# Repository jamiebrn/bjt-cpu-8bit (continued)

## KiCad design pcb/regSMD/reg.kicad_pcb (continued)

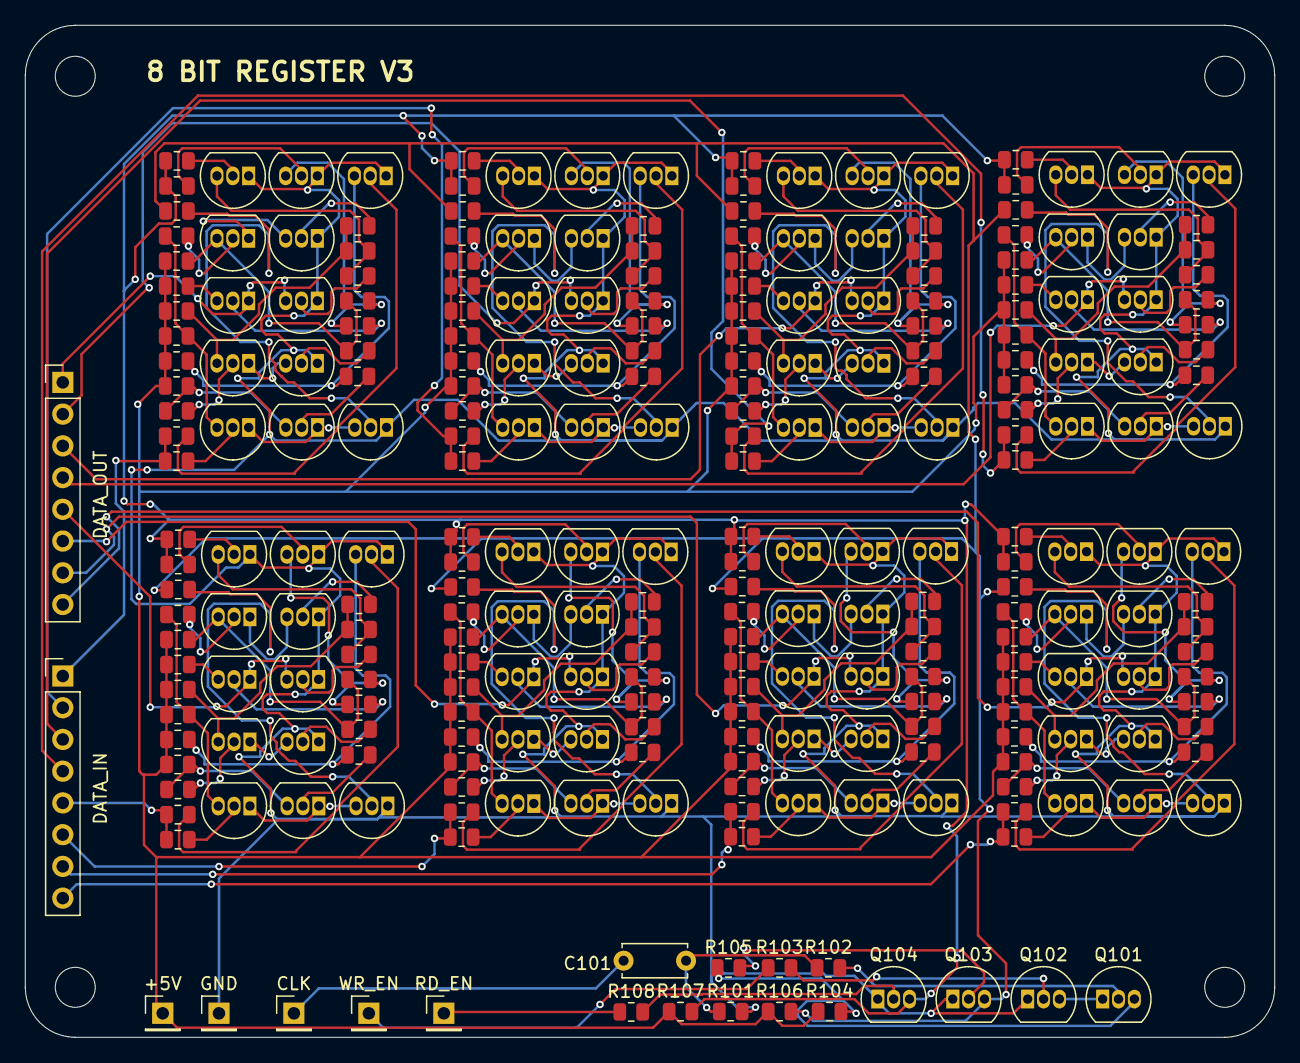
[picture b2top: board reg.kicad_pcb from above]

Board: 2 copper layers, 100.0 x 81.0 mm, 276 parts (0 on the bottom side), 214 nets.

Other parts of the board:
+5V: CLK; PinHeader_1x01_P2.54mm_Vertical
CLK: CLK; PinHeader_1x01_P2.54mm_Vertical
DATA_IN: Conn_01x08_Pin; PinHeader_1x08_P2.54mm_Vertical
DATA_OUT: Conn_01x08_Pin; PinHeader_1x08_P2.54mm_Vertical
GND: WRITE_EN; PinHeader_1x01_P2.54mm_Vertical
RD_EN: READ_EN; PinHeader_1x01_P2.54mm_Vertical
WR_EN: WRITE_EN; PinHeader_1x01_P2.54mm_Vertical

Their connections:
+5V: +5V.1; also elsewhere on the board
/DFlipFlop1/D: DATA_IN.2; also elsewhere on the board
/DFlipFlop1/Q: DATA_OUT.2; also elsewhere on the board
/DFlipFlop2/D: DATA_IN.3; also elsewhere on the board
/DFlipFlop2/Q: DATA_OUT.3; also elsewhere on the board
/DFlipFlop3/D: DATA_IN.4; also elsewhere on the board
/DFlipFlop3/Q: DATA_OUT.4; also elsewhere on the board
/DFlipFlop4/D: DATA_IN.5; also elsewhere on the board
/DFlipFlop4/Q: DATA_OUT.5; also elsewhere on the board
/DFlipFlop5/D: DATA_IN.6; also elsewhere on the board
/DFlipFlop5/Q: DATA_OUT.6; also elsewhere on the board
/DFlipFlop6/D: DATA_IN.7; also elsewhere on the board
/DFlipFlop6/Q: DATA_OUT.7; also elsewhere on the board
/DFlipFlop7/D: DATA_IN.8; also elsewhere on the board
/DFlipFlop7/Q: DATA_OUT.8; also elsewhere on the board
/DFlipFlop/D: DATA_IN.1; also elsewhere on the board
/DFlipFlop/Q: DATA_OUT.1; also elsewhere on the board
GND: GND.1; also elsewhere on the board
unnamed 20: CLK.1; also elsewhere on the board
unnamed 21: WR_EN.1; also elsewhere on the board
unnamed 22: RD_EN.1; also elsewhere on the board

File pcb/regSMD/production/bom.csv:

Designator,Footprint,Quantity,Value,LCSC Part #
"R101, R102, R103, R105, R108, R202, R203, R204, R205, R208, R209, R211, R212, R219, R220, R302, R303, R304, R305, R308, R309, R311, R312, R319, R320, R402, R403, R404, R405, R408, R409, R411, R412, R419, R420, R502, R503, R504, R505, R508, R509, R511, R512, R519, R520, R602, R603, R604, R605, R608, R609, R611, R612, R619, R620, R702, R703, R704, R705, R708, R709, R711, R712, R719, R720, R802, R803, R804, R805, R808, R809, R811, R812, R819, R820, R902, R903, R904, R905, R908, R909, R911, R912, R919, R920",0805,85,10000,
"R104, R106, R107, R201, R206, R207, R210, R213, R214, R215, R216, R217, R218, R301, R306, R307, R310, R313, R314, R315, R316, R317, R318, R401, R406, R407, R410, R413, R414, R415, R416, R417, R418, R501, R506, R507, R510, R513, R514, R515, R516, R517, R518, R601, R606, R607, R610, R613, R614, R615, R616, R617, R618, R701, R706, R707, R710, R713, R714, R715, R716, R717, R718, R801, R806, R807, R810, R813, R814, R815, R816, R817, R818, R901, R906, R907, R910, R913, R914, R915, R916, R917, R918",0805,83,4700,

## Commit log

2026-01-15 fixed 8bit reg v3 pcb
2026-01-15 start on logisim prototype + spec writeup/planning
2026-01-16 first complete specification draft
2026-01-16 some logisim shit
2026-01-17 logisim instruction fetching
2026-01-17 logisim instruction decoder
2026-01-18 logisim registers + complete ALU
2026-01-18 logisim full register + immediate decoding
2026-01-18 logisim simulation working, no stack operations yet :(
2026-01-18 isa modifications + logisim corrected decoding
2026-01-18 swapping isa around trying to simplify architecture. too tired rn
2026-01-19 starting to fall into place. giving me a headache
2026-01-20 variable cycle len instructions fucking with my design. but progress
2026-01-20 start on assembler
2026-01-22 started rebuild, actually planned instruction stages and became charles babbage
2026-01-22 i cannot use git
2026-01-23 seriously getting there. need to figure out timing of shift between fetch and operation
2026-01-23 im dumb and kept pop/ret stage order same as push/call
2026-01-23 instr stage timing working, now wiring control
2026-01-23 basic instructions functioning again
2026-01-23 progress on control signal wiring
2026-01-25 finished logisim build???
2026-01-25 holy logisim working build this is crazy
2026-01-25 before fix function calls
2026-01-26 ram clear
2026-01-26 nearly fully working, with function pointersgit add --all
2026-01-26 logisim done??
2026-01-26 assembler probably 60% done
2026-01-27 working assembler (i think??)
2026-01-27 assembler done with pseudo-ops
2026-01-27 removed assembler token output
2026-01-27 tiny bugs but basically all functioning :O
2026-01-28 assembler defines + label scope
2026-01-28 can't believe i uploaded an x86 binary
2026-01-28 assembler duplicate label fix + start on stdlib
2026-01-29 stdlib multiply
2026-01-29 start on memcmp
2026-01-29 memcmp
2026-01-29 dumb assembler formatting tweaks
2026-01-30 stdlib bit shifts
2026-01-30 start on video system
2026-01-31 ball + stdvideo
2026-02-01 start on emulator
2026-02-01 emulator progress, ugly ass code
2026-02-02 emulator implemented ISA
2026-02-02 emulator functions + ret
2026-02-02 fixed ret
2026-02-06 start on regv4
2026-02-06 emulator working (probably)
2026-02-06 start on emulator display
2026-02-06 regv4 rst
2026-02-06 emulator fixes
2026-02-07 small work on regv4 (so lazy)
2026-02-27 readme init
